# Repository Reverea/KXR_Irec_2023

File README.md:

# KXR_Irec_2023
Knights Experimental Rocketry payloads resources for IREC 2023

## Structure
The payloads system of the UCF KXR 2023 IREC Hybrid Rocket will only be used for experiments, video recording/transmission, and data recording/transmission. All recovery hardware will be commercial. 

The payloads system consists of three main PCBs, each with a specialized purpose to allow for modularity. The PCBs will communicate over a CAN bus. The three PCBs are as follows:
1. Power Board: Regulate 4s Lipo to 12v, measure current and voltage and different points, control and distribute power to different systems. 
2. Main Avionics Board: Gather sensor data, record sensor data, manage data between different boards.
3. Nosecone Board: Receive GPS data, transmit/receive telemetry, control power to video RF amp. 

This repository contains the Nosecone and Power PCBs as those were the two that I designed.

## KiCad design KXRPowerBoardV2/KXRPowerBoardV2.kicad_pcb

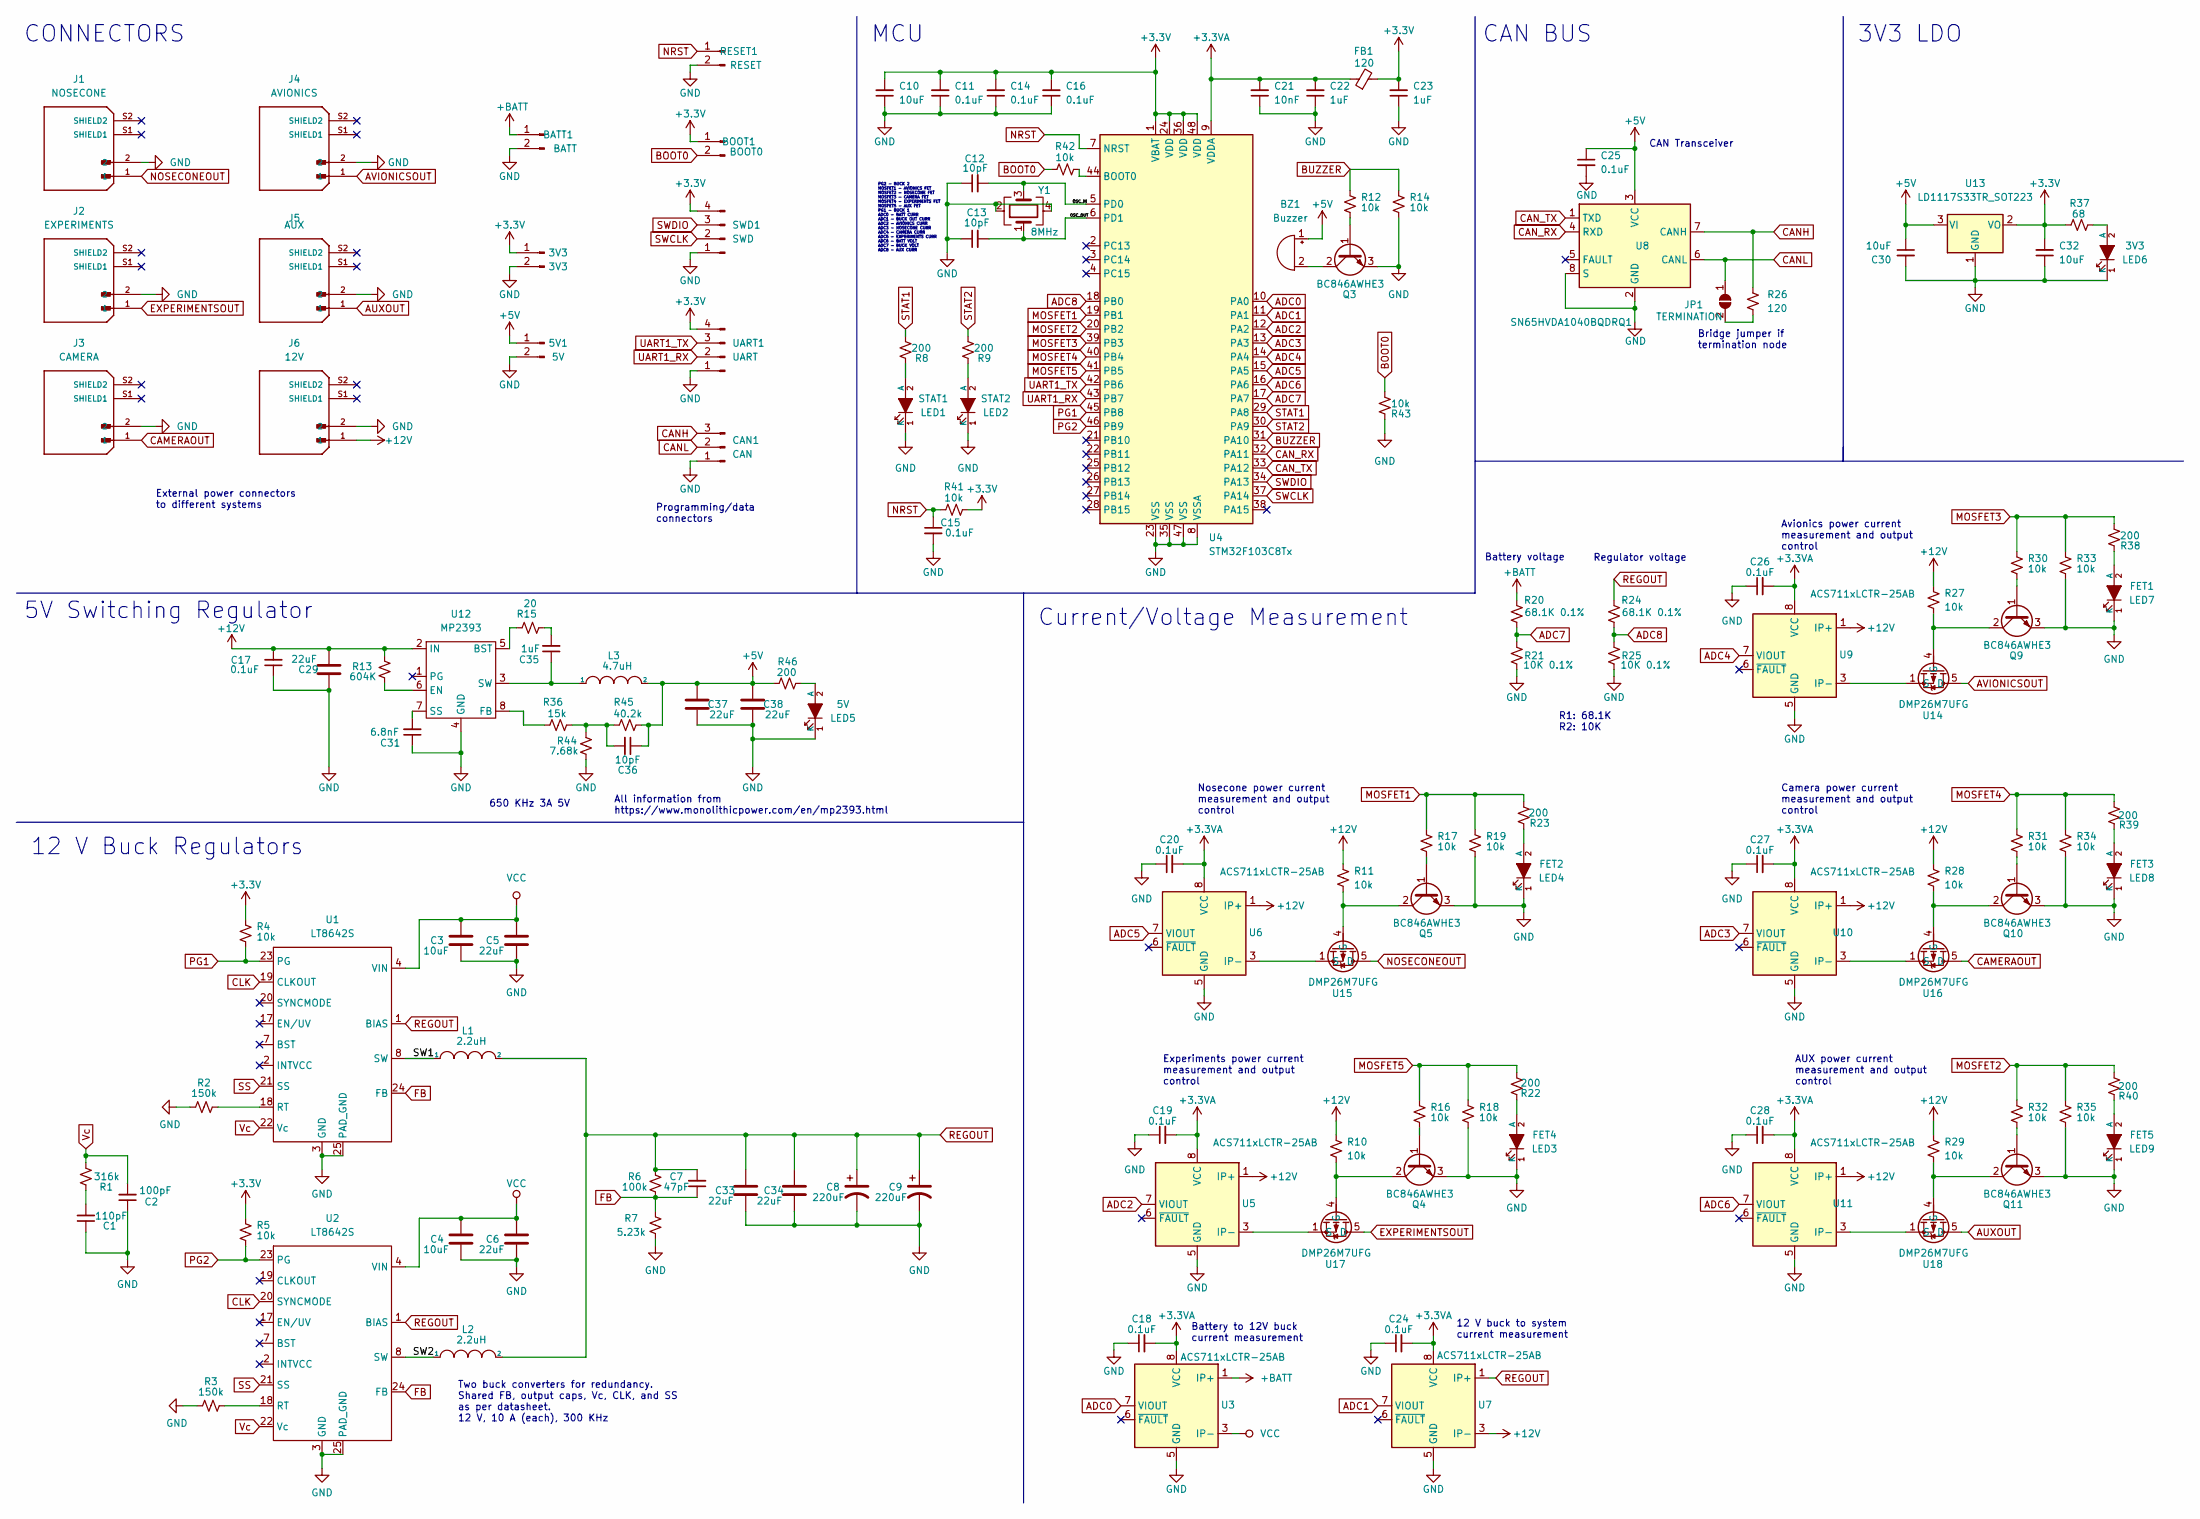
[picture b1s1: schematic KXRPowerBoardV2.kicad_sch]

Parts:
3V3: 3V3; PinHeader_1x02_P2.54mm_Vertical
5V1: 5V; PinHeader_1x02_P2.54mm_Vertical
BATT1: BATT; Molex_KK-396_A-41791-0002_1x02_P3.96mm_Vertical
BOOT1: BOOT0; PinHeader_1x02_P2.54mm_Vertical
BZ1: Buzzer; MagneticBuzzer_PUI_AT-0927-TT-6-R
C1: 110pF; C_0402_1005Metric
C2: 100pF; C_0402_1005Metric
C3, C4, C30, C32: 10uF; C_1206_3216Metric
C5, C6, C29, C33, C34, C37, C38: 22uF; C_1210_3225Metric
C7: 47pF; C_0402_1005Metric
C8, C9: 220uF; CP_Radial_D8.0mm_P3.50mm
C10: 10uF; C_0805_2012Metric
C11, C14, C15, C16, C17, C18, C19, C20, C24, C25, C26, C27, C28: 0.1uF; C_0402_1005Metric
C12, C13, C36: 10pF; C_0402_1005Metric
C21: 10nF; C_0402_1005Metric
C22, C23, C35: 1uF; C_0402_1005Metric
C31: 6.8nF; C_0402_1005Metric
CAN1: CAN; Molex_PicoBlade_53048-0310_1x03_P1.25mm_Horizontal
FB1: 120; L_0603_1608Metric
J1: NOSECONE; MOLEX_436500203; PARTREV F3
J2: EXPERIMENTS; MOLEX_436500203; PARTREV F3
J3: CAMERA; MOLEX_436500203; PARTREV F3
J4: AVIONICS; MOLEX_436500203; PARTREV F3
J5: AUX; MOLEX_436500203; PARTREV F3
J6: 12V; MOLEX_436500203; PARTREV F3
JP1: TERMINATION; SolderJumper-2_P1.3mm_Open_RoundedPad1.0x1.5mm
L1, L2: 2.2uH; XAL7070-222MEC
L3: 4.7uH; MGAH06034R7M
LED1: STAT1; LED_0603_1608Metric
LED2: STAT2; LED_0603_1608Metric
LED3: FET4; LED_0603_1608Metric
LED4: FET2; LED_0603_1608Metric
LED5: 5V; LED_0603_1608Metric
LED6: 3V3; LED_0603_1608Metric
LED7: FET1; LED_0603_1608Metric
LED8: FET3; LED_0603_1608Metric
LED9: FET5; LED_0603_1608Metric
Q3, Q4, Q5, Q9, Q10, Q11: BC846AWHE3; SOT-323_SC-70
R1: 316k; R_0402_1005Metric
R2, R3: 150k; R_0402_1005Metric
R4, R5, R10, R11, R12, R14, R16, R17, R18, R19, R27, R28, R29, R30, R31, R32, R33, R34, R35, R41, R42, R43: 10k; R_0402_1005Metric
R6: 100k; R_0402_1005Metric
R7: 5.23k; R_0402_1005Metric
R8, R9, R22, R23, R38, R39, R40, R46: 200; R_0402_1005Metric
R13: 604K; R_0402_1005Metric
R15: 20; R_0402_1005Metric
R20, R24: 68.1K 0.1%; R_0402_1005Metric
R21, R25: 10K 0.1%; R_0402_1005Metric
R26: 120; R_0402_1005Metric
R36: 15k; R_0402_1005Metric
R37: 68; R_0402_1005Metric
R44: 7.68k; R_0402_1005Metric
R45: 40.2k; R_0402_1005Metric
RESET1: RESET; PinHeader_1x02_P2.54mm_Vertical
SWD1: SWD; PinHeader_1x04_P2.54mm_Vertical
U1, U2: LT8642S; LT8642SIVPBF
U3, U5, U6, U7, U9, U10, U11: ACS711xLCTR-25AB; SOIC-8_3.9x4.9mm_P1.27mm
U4: STM32F103C8Tx; LQFP-48_7x7mm_P0.5mm
U8: SN65HVDA1040BQDRQ1; SOIC-8_3.9x4.9mm_P1.27mm
U12: MP2393; SOTFL50P160X60-8N
U13: LD1117S33TR_SOT223; SOT-223-3_TabPin2
U14, U15, U16, U17, U18: DMP26M7UFG; Diodes_PowerDI3333-8
UART1: UART; PinHeader_1x04_P2.54mm_Vertical
Y1: 8MHz; Crystal_SMD_3225-4Pin_3.2x2.5mm

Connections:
Vc: C2.2, R1.1, U1.22 (Vc), U2.22 (Vc)
+3.3VA: C18.2, C19.2, C20.2, C21.2, C22.2, C24.2, C26.2, C27.2, C28.2, FB1.1, U3.8 (VCC), U4.9 (VDDA), U5.8 (VCC), U6.8 (VCC), U7.8 (VCC), U9.8 (VCC), U10.8 (VCC), U11.8 (VCC)
+5V: 5V1.1, BZ1.1 (-), C25.1, C30.1, C36.1, C37.1, C38.1, L3.2, R45.2, R46.1, U8.3 (VCC), U13.3 (VI)
+BATT: BATT1.1, R20.1, U3.1 (IP+), U3.2 (IP+)
/OSC_IN: C12.2, U4.5 (PD0), Y1.3
/OSC_OUT: C13.2, U4.6 (PD1), Y1.1
/SW1: L1.1, U1.8 (SW), U1.9 (SW), U1.10 (SW), U1.11 (SW), U1.12 (SW)
/SW2: L2.1, U2.8 (SW), U2.9 (SW), U2.10 (SW), U2.11 (SW), U2.12 (SW)
ADC0: U3.7 (VIOUT), U4.10 (PA0)
ADC1: U4.11 (PA1), U7.7 (VIOUT)
ADC2: U4.12 (PA2), U5.7 (VIOUT)
ADC3: U4.13 (PA3), U10.7 (VIOUT)
ADC4: U4.14 (PA4), U9.7 (VIOUT)
ADC5: U4.15 (PA5), U6.7 (VIOUT)
ADC6: U4.16 (PA6), U11.7 (VIOUT)
ADC7: R20.2, R21.1, U4.17 (PA7)
ADC8: R24.2, R25.1, U4.18 (PB0)
AUXOUT: J5.1, U18.5 (D)
AVIONICSOUT: J4.1, U14.5 (D)
BOOT0: BOOT1.2, R42.2, R43.1
BUZZER: R12.1, R14.1, U4.31 (PA10)
CAMERAOUT: J3.1, U16.5 (D)
CANH: CAN1.3, R26.1, U8.7 (CANH)
CANL: CAN1.2, JP1.1 (A), U8.6 (CANL)
CAN_RX: U4.32 (PA11), U8.4 (RXD)
CAN_TX: U4.33 (PA12), U8.1 (TXD)
CLK: U1.19 (CLKOUT), U2.20 (SYNCMODE)
EXPERIMENTSOUT: J2.1, U17.5 (D)
FB: C7.1, R6.2, R7.1, U1.24 (FB), U2.24 (FB)
GND: 3V3.2, 5V1.2, BATT1.2, C1.1, C2.1, C3.2, C4.2, C5.2, C6.2, C8.2, C9.2, C10.1, C11.1, C12.1, C13.1, C14.1, C15.2, C16.1, C17.1, C18.1, C19.1, C20.1, C21.1, C22.1, C23.1, C24.1, C25.2, C26.1, C27.1, C28.1, C29.1, C30.2, C31.1, C32.1, C33.2, C34.2, C37.2, C38.2, CAN1.1, J1.2, J2.2, J3.2, J4.2, J5.2, J6.2, LED1.1 (K), LED2.1 (K), LED3.1 (K), LED4.1 (K), LED5.1 (K), LED6.1 (K), LED7.1 (K), LED8.1 (K), LED9.1 (K), Q3.3 (E), Q4.3 (E), Q5.3 (E), Q9.3 (E), Q10.3 (E), Q11.3 (E), R2.2, R3.2, R7.2, R14.2, R18.2, R19.2, R21.2, R25.2, R33.2, R34.2, R35.2, R43.2, R44.1, RESET1.2, SWD1.1, U1.3 (GND), U1.16 (GND), U1.25 (PAD_GND), U1.26 (PAD_GND), U1.27 (PAD_GND), U1.28 (PAD_GND), U2.3 (GND), U2.16 (GND), U2.25 (PAD_GND), U2.26 (PAD_GND), U2.27 (PAD_GND), U2.28 (PAD_GND), U3.5 (GND), U4.8 (VSSA), U4.23 (VSS), U4.35 (VSS), U4.47 (VSS), U5.5 (GND), U6.5 (GND), U7.5 (GND), U8.2 (GND), U8.8 (S), U9.5 (GND), U10.5 (GND), U11.5 (GND), U12.4 (GND), U13.1 (GND), UART1.1, Y1.2, Y1.4; also elsewhere on the board
MOSFET1: R17.1, R19.1, R23.1, U4.19 (PB1)
MOSFET2: R32.1, R35.1, R40.1, U4.20 (PB2)
MOSFET3: R30.1, R33.1, R38.1, U4.39 (PB3)
MOSFET4: R31.1, R34.1, R39.1, U4.40 (PB4)
MOSFET5: R16.1, R18.1, R22.1, U4.41 (PB5)
NOSECONEOUT: J1.1, U15.5 (D)
NRST: C15.1, R41.2, RESET1.1, U4.7 (NRST)
unnamed: BZ1.2 (+), Q3.2 (C)
unnamed: C1.2, R1.2
unnamed: C31.2, U12.7 (SS)
unnamed: C35.1, L3.1, U12.3 (SW)
unnamed: C35.2, R15.2
unnamed: C36.2, R36.2, R44.2, R45.1
unnamed: JP1.2 (B), R26.2
unnamed: LED1.2 (A), R8.2
unnamed: LED2.2 (A), R9.2
unnamed: LED3.2 (A), R22.2
unnamed: LED4.2 (A), R23.2
unnamed: LED5.2 (A), R46.2
unnamed: LED6.2 (A), R37.2
unnamed: LED7.2 (A), R38.2
unnamed: LED8.2 (A), R39.2
unnamed: LED9.2 (A), R40.2
unnamed: Q3.1 (B), R12.2
unnamed: Q4.1 (B), R16.2
unnamed: Q4.2 (C), R10.2, U17.4 (G)
unnamed: Q5.1 (B), R17.2
unnamed: Q5.2 (C), R11.2, U15.4 (G)
unnamed: Q9.1 (B), R30.2
unnamed: Q9.2 (C), R27.2, U14.4 (G)
unnamed: Q10.1 (B), R31.2
unnamed: Q10.2 (C), R28.2, U16.4 (G)
unnamed: Q11.1 (B), R32.2
unnamed: Q11.2 (C), R29.2, U18.4 (G)
unnamed: R2.1, U1.18 (RT)
unnamed: R3.1, U2.18 (RT)
unnamed: R13.1, U12.6 (EN)
unnamed: R15.1, U12.5 (BST)
unnamed: R36.1, U12.8 (FB)
unnamed: R42.1, U4.44 (BOOT0)
unnamed: U10.3 (IP-), U10.4 (IP-), U16.1 (S), U16.2 (S), U16.3 (S)
unnamed: U11.3 (IP-), U11.4 (IP-), U18.1 (S), U18.2 (S), U18.3 (S)
unnamed: U9.3 (IP-), U9.4 (IP-), U14.1 (S), U14.2 (S), U14.3 (S)
unnamed: U6.3 (IP-), U6.4 (IP-), U15.1 (S), U15.2 (S), U15.3 (S)
unnamed: U5.3 (IP-), U5.4 (IP-), U17.1 (S), U17.2 (S), U17.3 (S)
PG1: R4.2, U1.23 (PG), U4.45 (PB8)
PG2: R5.2, U2.23 (PG), U4.46 (PB9)
REGOUT: C7.2, C8.1, C9.1, C33.1, C34.1, L1.2, L2.2, R6.1, R24.1, U1.1 (BIAS), U2.1 (BIAS), U7.1 (IP+), U7.2 (IP+)
SS: U1.21 (SS), U2.21 (SS)
STAT1: R8.1, U4.29 (PA8)
STAT2: R9.1, U4.30 (PA9)
SWCLK: SWD1.2, U4.37 (PA14)
SWDIO: SWD1.3, U4.34 (PA13)
UART1_RX: U4.43 (PB7), UART1.2
UART1_TX: U4.42 (PB6), UART1.3
VCC: C3.1, C4.1, C5.1, C6.1, U1.4 (VIN), U1.5 (VIN), U1.6 (VIN), U1.13 (VIN), U1.14 (VIN), U1.15 (VIN), U2.4 (VIN), U2.5 (VIN), U2.6 (VIN), U2.13 (VIN), U2.14 (VIN), U2.15 (VIN), U3.3 (IP-), U3.4 (IP-)

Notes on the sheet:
PG2 - BUCK 2 MOSFET1 - AVIONICS FET MOSFET2 - NOSECONE FET MOSFET3 - CAMERA FET MOSFET4 - EXPERIMENTS FET MOSFET5 - AUX FET PG1 - BUCK 1 ADC0 - BATT CURR ADC1 - BUCK OUT CURR ADC2 - AVIONICS CURR ADC3 - NOSECONE CURR ADC4 - CAMERA CURR ADC5 - EXPERIMENTS CURR ADC6 - BATT VOLT ADC7 - BUCK VOLT ADC8 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
R1: 68.1K R2: 10K
Camera power current measurement and output control
CAN BUS
Experiments power current measurement and output control
12 V buck to system current measurement
Current/Voltage Measurement
Regulator voltage
Nosecone power current measurement and output control
AUX power current measurement and output control
Two buck converters for redundancy. Shared FB, output caps, Vc, CLK, and SS as per datasheet. 12 V, 10 A (each), 300 KHz
12 V Buck Regulators
Avionics power current measurement and output control
Battery voltage
All information from https://www.monolithicpower.com/en/mp2393.html
CAN Transceiver
3V3 LDO
5V Switching Regulator
Programming/data connectors
CONNECTORS
Bridge jumper if termination node
MCU
650 KHz 3A 5V
External power connectors to different systems
Battery to 12V buck current measurement

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
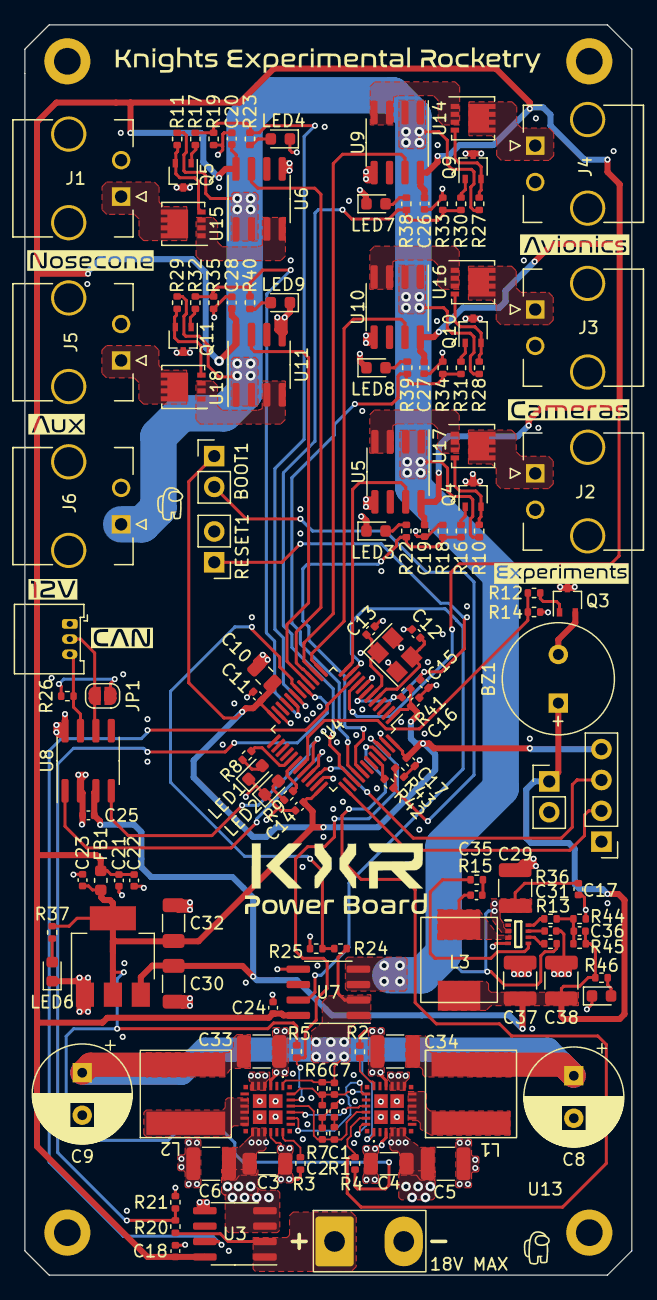
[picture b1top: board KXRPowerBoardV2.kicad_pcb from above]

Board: 4 copper layers, 50.0 x 103.0 mm, 137 parts (0 on the bottom side), 86 nets.

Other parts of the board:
C17#2: 0.1uF; C_0402_1005Metric

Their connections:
GND: C17#2.1; also elsewhere on the board

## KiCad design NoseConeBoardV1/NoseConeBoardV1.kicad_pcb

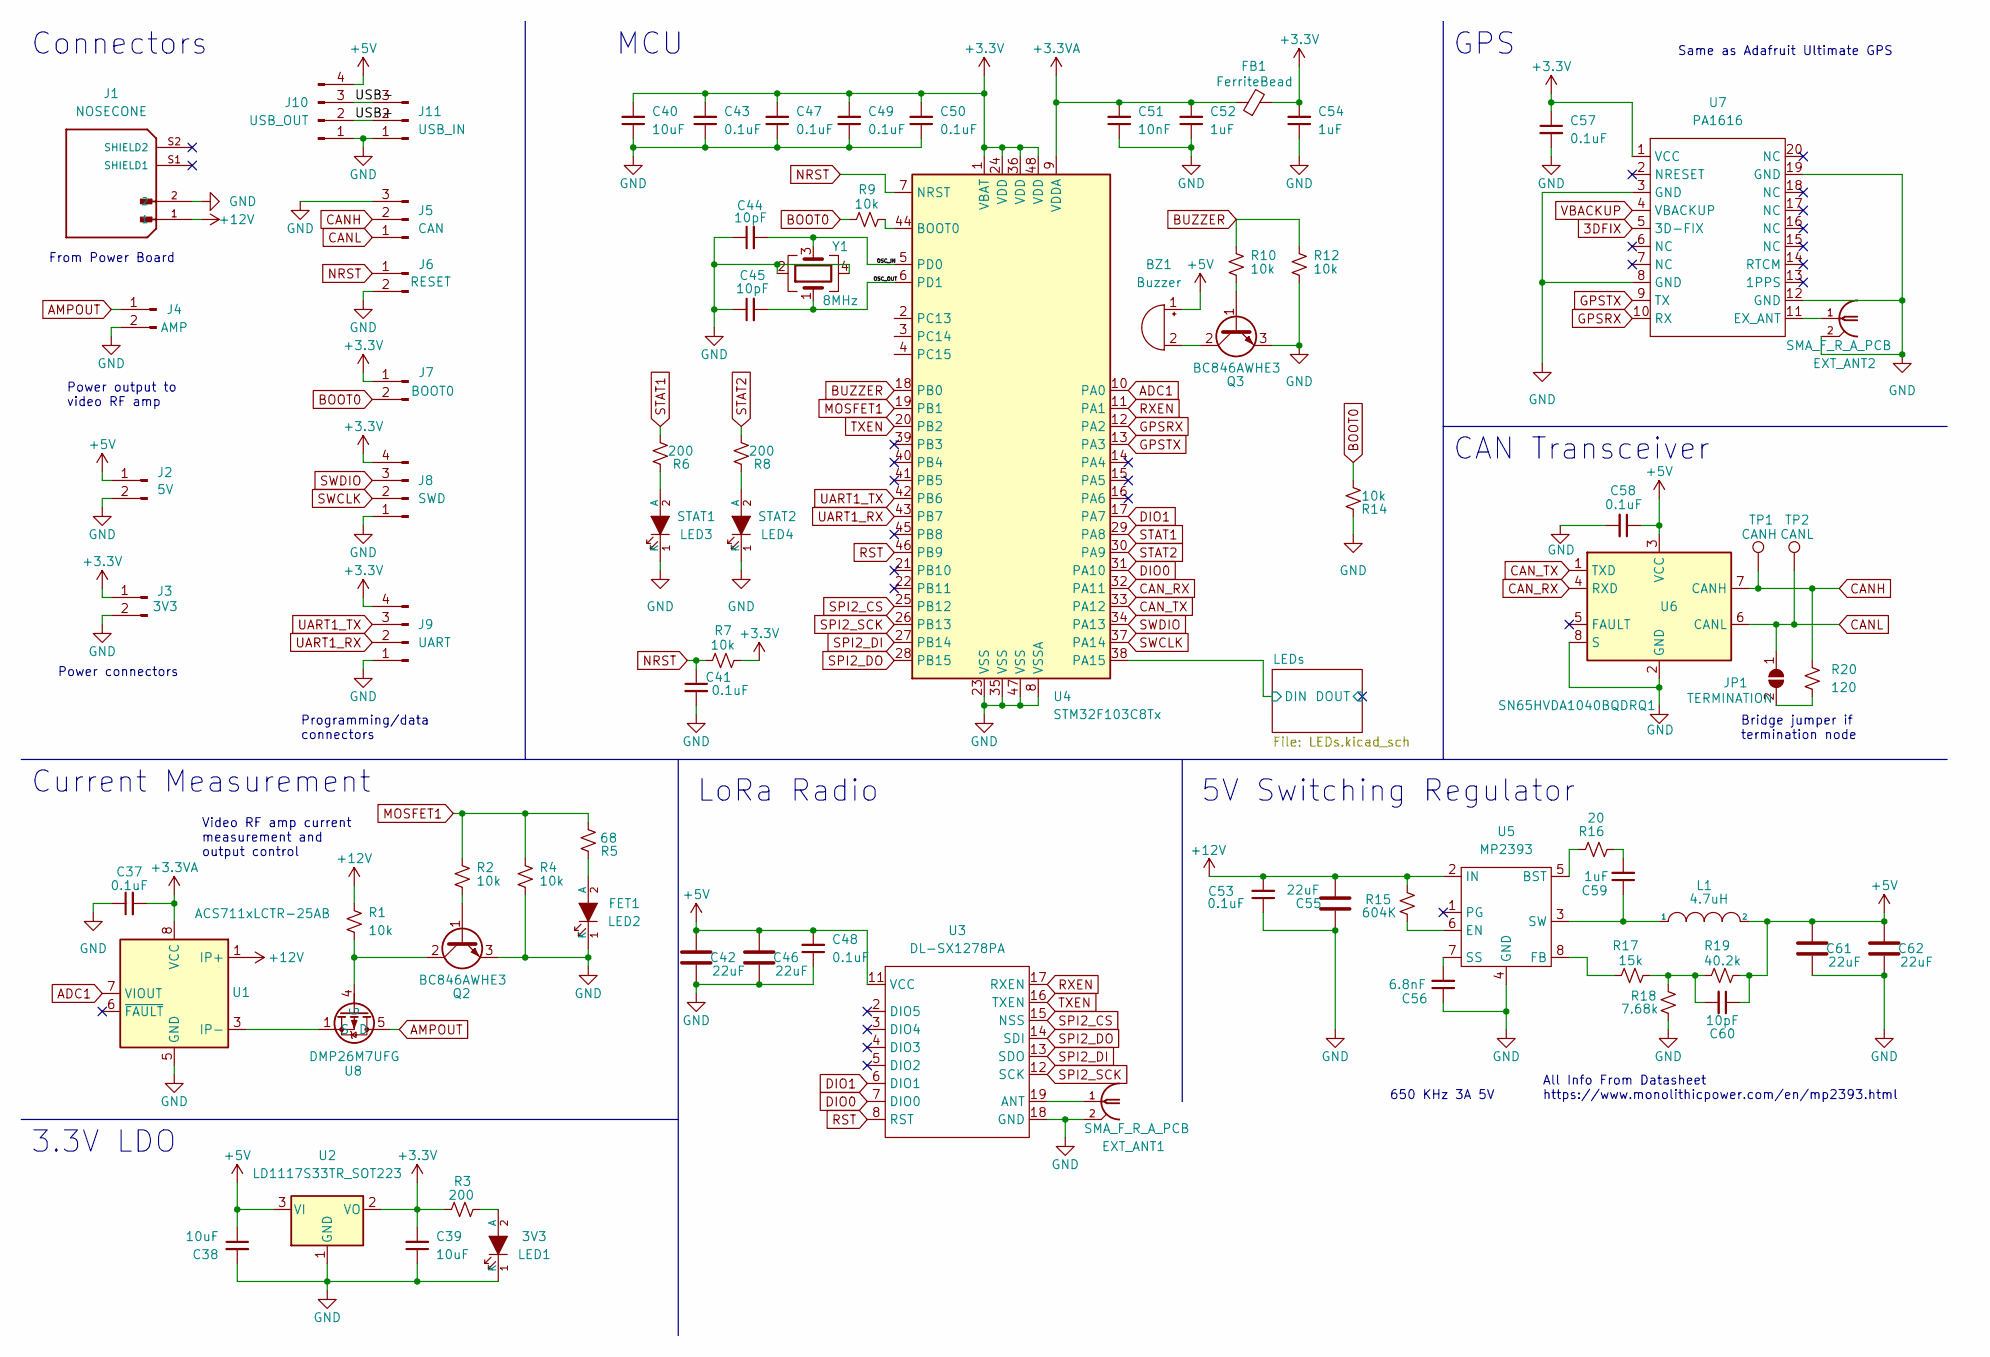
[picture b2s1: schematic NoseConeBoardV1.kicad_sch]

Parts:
BZ1: Buzzer; MagneticBuzzer_PUI_AT-0927-TT-6-R
C37, C41, C43, C47, C48, C49, C50, C53, C57, C58: 0.1uF; C_0402_1005Metric
C38, C39, C40: 10uF; C_1206_3216Metric
C42, C46, C55, C61, C62: 22uF; C_1210_3225Metric
C44, C45, C60: 10pF; C_0402_1005Metric
C51: 10nF; C_0402_1005Metric
C52, C54, C59: 1uF; C_0402_1005Metric
C56: 6.8nF; C_0402_1005Metric
EXT_ANT1, EXT_ANT2: SMA_F_R_A_PCB; SMA_Amphenol_901-144_Vertical
FB1: FerriteBead; L_0603_1608Metric
J1: NOSECONE; MOLEX_436500203; PARTREV F3
J2: 5V; PinSocket_1x02_P2.54mm_Vertical
J3: 3V3; PinSocket_1x02_P2.54mm_Vertical
J4: AMP; PinSocket_1x02_P2.54mm_Vertical
J5: CAN; Molex_PicoBlade_53048-0310_1x03_P1.25mm_Horizontal
J6: RESET; PinSocket_1x02_P2.54mm_Vertical
J7: BOOT0; PinSocket_1x02_P2.54mm_Vertical
J8: SWD; PinSocket_1x04_P2.54mm_Vertical
J9: UART; PinSocket_1x04_P2.54mm_Vertical
J10: USB_OUT; PinSocket_1x04_P2.54mm_Vertical
J11: USB_IN; Molex_PicoBlade_53048-0310_1x03_P1.25mm_Horizontal
JP1: TERMINATION; SolderJumper-2_P1.3mm_Open_RoundedPad1.0x1.5mm
L1: 4.7uH; MGAH06034R7M
LED1: 3V3; LED_0603_1608Metric
LED2: FET1; LED_0603_1608Metric
LED3: STAT1; LED_0603_1608Metric
LED4: STAT2; LED_0603_1608Metric
Q2, Q3: BC846AWHE3; SOT-323_SC-70
R1, R2, R4, R7, R9, R10, R12, R14: 10k; R_0402_1005Metric
R3, R6, R8: 200; R_0402_1005Metric
R5: 68; R_0402_1005Metric
R15: 604K; R_0402_1005Metric
R16: 20; R_0402_1005Metric
R17: 15k; R_0402_1005Metric
R18: 7.68k; R_0402_1005Metric
R19: 40.2k; R_0402_1005Metric
R20: 120; R_0402_1005Metric
TP1: CANH; TestPoint_Pad_D1.0mm
TP2: CANL; TestPoint_Pad_D1.0mm
U1: ACS711xLCTR-25AB; SOIC-8_3.9x4.9mm_P1.27mm
U2: LD1117S33TR_SOT223; SOT-223-3_TabPin2
U3: DL-SX1278PA
U4: STM32F103C8Tx; LQFP-48_7x7mm_P0.5mm
U5: MP2393; SOTFL50P160X60-8N
U6: SN65HVDA1040BQDRQ1; SOIC-8_3.9x4.9mm_P1.27mm
U7: PA1616
U8: DMP26M7UFG; Diodes_PowerDI3333-8
Y1: 8MHz; Crystal_SMD_3225-4Pin_3.2x2.5mm

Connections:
3DFIX: U7.5 (3D-FIX)
+3.3VA: C37.2, C51.2, C52.2, FB1.1, U1.8 (VCC), U4.9 (VDDA)
+3V3: C39.2, C40.2, C43.2, C47.2, C49.2, C50.2, C54.2, C57.1, FB1.2, J3.1, J7.1, J8.4, J9.4, R3.1, R7.1, U2.2 (VO), U4.1 (VBAT), U4.24 (VDD), U4.36 (VDD), U4.48 (VDD), U7.1 (VCC)
+5V: BZ1.1 (-), C38.1, C42.1, C46.1, C48.2, C58.1, C60.1, C61.1, C62.1, J2.1, J10.4, L1.2, R19.2, U2.3 (VI), U3.11 (VCC), U6.3 (VCC); also elsewhere on the board
+12V: C53.2, C55.2, J1.1, R1.1, R15.2, U1.1 (IP+), U1.2 (IP+), U5.2 (IN)
/LEDs/DIN: U4.38 (PA15); also elsewhere on the board
/OSC_IN: C44.2, U4.5 (PD0), Y1.3
/OSC_OUT: C45.2, U4.6 (PD1), Y1.1
/USB+: J10.2, J11.2
/USB-: J10.3, J11.3
ADC1: U1.7 (VIOUT), U4.10 (PA0)
AMPOUT: J4.1, U8.5 (D)
BOOT0: J7.2, R9.2, R14.1
BUZZER: R10.1, R12.1, U4.18 (PB0)
CANH: J5.2, R20.1, TP1.1, U6.7 (CANH)
CANL: J5.1, JP1.1 (A), TP2.1, U6.6 (CANL)
CAN_RX: U4.32 (PA11), U6.4 (RXD)
CAN_TX: U4.33 (PA12), U6.1 (TXD)
DIO0: U3.7 (DIO0), U4.31 (PA10)
DIO1: U3.6 (DIO1), U4.17 (PA7)
GND: C37.1, C38.2, C39.1, C40.1, C41.2, C42.2, C43.1, C44.1, C45.1, C46.2, C47.1, C48.1, C49.1, C50.1, C51.1, C52.1, C53.1, C54.1, C55.1, C56.1, C57.2, C58.2, C61.2, C62.2, EXT_ANT1.2, EXT_ANT1.3, EXT_ANT1.4, EXT_ANT1.5, EXT_ANT2.2, EXT_ANT2.3, EXT_ANT2.4, EXT_ANT2.5, J1.2, J2.2, J3.2, J4.2, J5.3, J6.2, J8.1, J9.1, J10.1, J11.1, LED1.1 (K), LED2.1 (K), LED3.1 (K), LED4.1 (K), Q2.3 (E), Q3.3 (E), R4.2, R12.2, R14.2, R18.1, U1.5 (GND), U2.1 (GND), U3.1 (GND), U3.9 (GND), U3.10 (GND), U3.18 (GND), U3.20 (GND), U3.21 (GND), U3.22 (GND), U4.8 (VSSA), U4.23 (VSS), U4.35 (VSS), U4.47 (VSS), U5.4 (GND), U6.2 (GND), U6.8 (S), U7.3 (GND), U7.8 (GND), U7.12 (GND), U7.19 (GND), Y1.2, Y1.4; also elsewhere on the board
GPSRX: U4.12 (PA2), U7.10 (RX)
GPSTX: U4.13 (PA3), U7.9 (TX)
MOSFET1: R2.1, R4.1, R5.1, U4.19 (PB1)
NRST: C41.1, J6.1, R7.2, U4.7 (NRST)
unnamed: BZ1.2 (+), Q3.2 (C)
unnamed: C56.2, U5.7 (SS)
unnamed: C59.1, L1.1, U5.3 (SW)
unnamed: C59.2, R16.2
unnamed: C60.2, R17.2, R18.2, R19.1
unnamed: EXT_ANT1.1, U3.19 (ANT)
unnamed: EXT_ANT2.1, U7.11 (EX_ANT)
unnamed: JP1.2 (B), R20.2
unnamed: LED1.2 (A), R3.2
unnamed: LED2.2 (A), R5.2
unnamed: LED3.2 (A), R6.2
unnamed: LED4.2 (A), R8.2
unnamed: Q2.1 (B), R2.2
unnamed: Q2.2 (C), R1.2, U8.4 (G)
unnamed: Q3.1 (B), R10.2
unnamed: R9.1, U4.44 (BOOT0)
unnamed: R15.1, U5.6 (EN)
unnamed: R16.1, U5.5 (BST)
unnamed: R17.1, U5.8 (FB)
unnamed: U1.3 (IP-), U1.4 (IP-), U8.1 (S), U8.2 (S), U8.3 (S)
RST: U3.8 (RST), U4.46 (PB9)
RXEN: U3.17 (RXEN), U4.11 (PA1)
SPI2_CS: U3.15 (NSS), U4.25 (PB12)
SPI2_DI: U3.13 (SDO), U4.27 (PB14)
SPI2_DO: U3.14 (SDI), U4.28 (PB15)
SPI2_SCK: U3.12 (SCK), U4.26 (PB13)
STAT1: R6.1, U4.29 (PA8)
STAT2: R8.1, U4.30 (PA9)
SWCLK: J8.2, U4.37 (PA14)
SWDIO: J8.3, U4.34 (PA13)
TXEN: U3.16 (TXEN), U4.20 (PB2)
UART1_RX: J9.2, U4.43 (PB7)
UART1_TX: J9.3, U4.42 (PB6)
VBACKUP: U7.4 (VBACKUP)

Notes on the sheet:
CAN Transceiver
Video RF amp current measurement and output control
5V Switching Regulator
Power connectors
LoRa Radio
MCU
3.3V LDO
Connectors
All Info From Datasheet https://www.monolithicpower.com/en/mp2393.html
Programming/data connectors
Current Measurement
Power output to video RF amp
Same as Adafruit Ultimate GPS
Bridge jumper if termination node
GPS
650 KHz 3A 5V
From Power Board

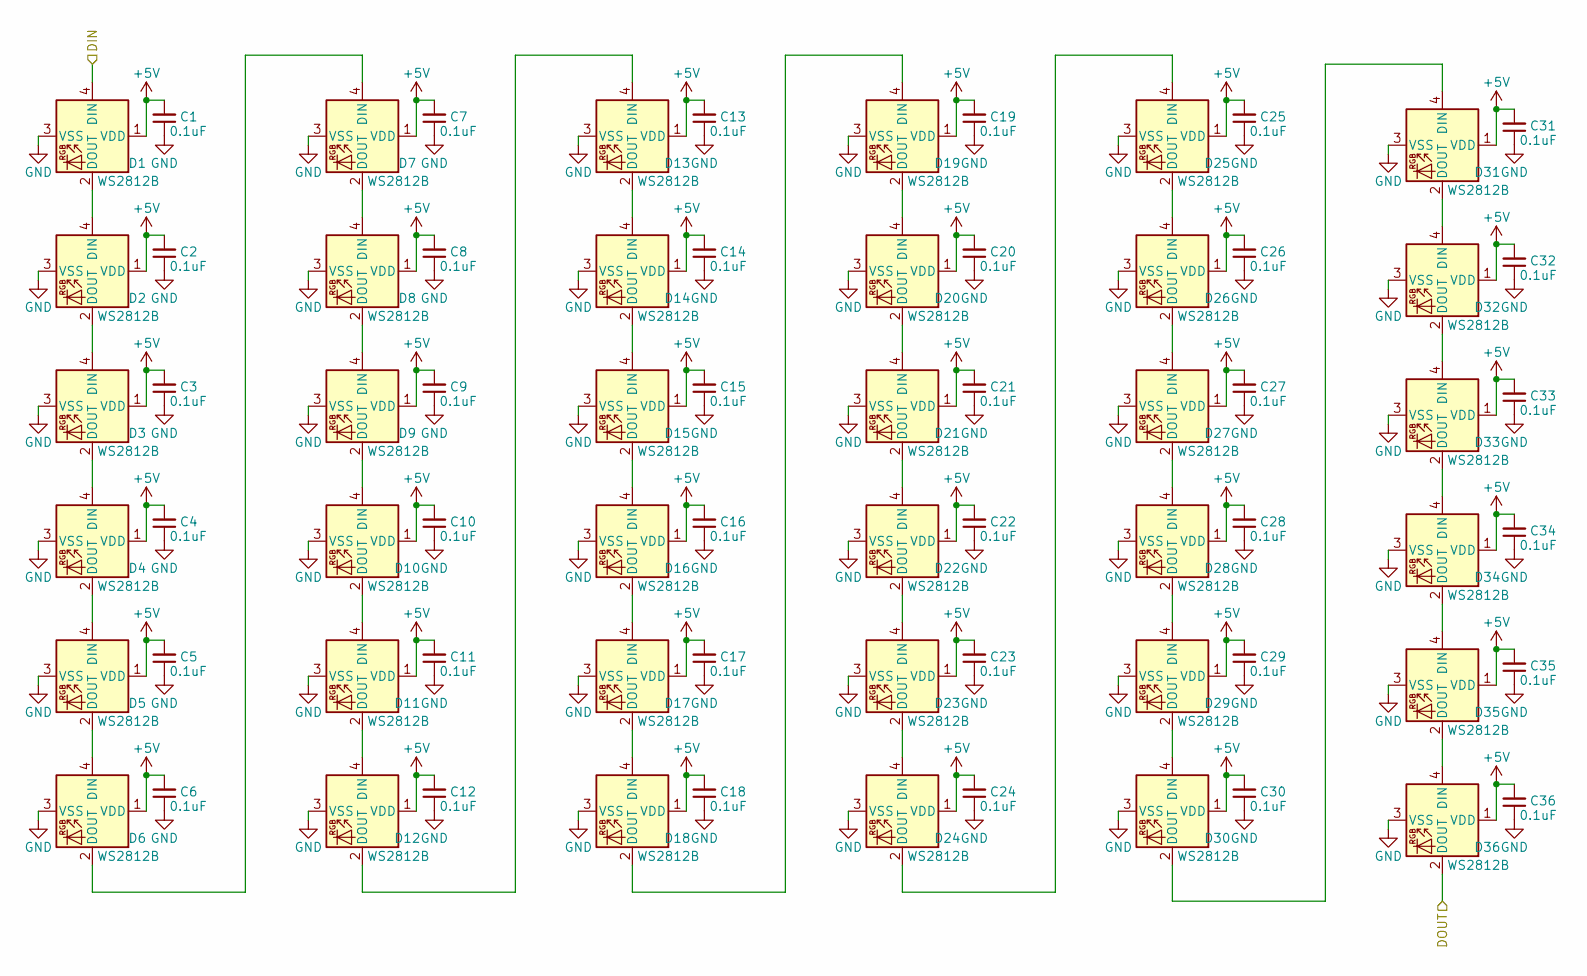
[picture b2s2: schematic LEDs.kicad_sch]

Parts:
C1, C2, C3, C4, C5, C6, C7, C8, C9, C10, C11, C12, C13, C14, C15, C16, C17, C18, C19, C20, C21, C22, C23, C24, C25, C26, C27, C28, C29, C30, C31, C32, C33, C34, C35, C36: 0.1uF; C_0402_1005Metric
D1, D2, D3, D4, D5, D6, D7, D8, D9, D10, D11, D12, D13, D14, D15, D16, D17, D18, D19, D20, D21, D22, D23, D24, D25, D26, D27, D28, D29, D30, D31, D32, D33, D34, D35, D36: WS2812B; LED_WS2812B_PLCC4_5.0x5.0mm_P3.2mm

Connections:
+5V: C1.2, C2.2, C3.2, C4.2, C5.2, C6.2, C7.2, C8.2, C9.2, C10.2, C11.2, C12.2, C13.2, C14.2, C15.2, C16.2, C17.2, C18.2, C19.2, C20.2, C21.2, C22.2, C23.2, C24.2, C25.2, C26.2, C27.2, C28.2, C29.2, C30.2, C31.2, C32.2, C33.2, C34.2, C35.2, C36.2, D1.1 (VDD), D2.1 (VDD), D3.1 (VDD), D4.1 (VDD), D5.1 (VDD), D6.1 (VDD), D7.1 (VDD), D8.1 (VDD), D9.1 (VDD), D10.1 (VDD), D11.1 (VDD), D12.1 (VDD), D13.1 (VDD), D14.1 (VDD), D15.1 (VDD), D16.1 (VDD), D17.1 (VDD), D18.1 (VDD), D19.1 (VDD), D20.1 (VDD), D21.1 (VDD), D22.1 (VDD), D23.1 (VDD), D24.1 (VDD), D25.1 (VDD), D26.1 (VDD), D27.1 (VDD), D28.1 (VDD), D29.1 (VDD), D30.1 (VDD), D31.1 (VDD), D32.1 (VDD), D33.1 (VDD), D34.1 (VDD), D35.1 (VDD), D36.1 (VDD); also elsewhere on the board
/LEDs/DIN: D1.4 (DIN); also elsewhere on the board
/LEDs/DOUT: D36.2 (DOUT)
GND: C1.1, C2.1, C3.1, C4.1, C5.1, C6.1, C7.1, C8.1, C9.1, C10.1, C11.1, C12.1, C13.1, C14.1, C15.1, C16.1, C17.1, C18.1, C19.1, C20.1, C21.1, C22.1, C23.1, C24.1, C25.1, C26.1, C27.1, C28.1, C29.1, C30.1, C31.1, C32.1, C33.1, C34.1, C35.1, C36.1, D1.3 (VSS), D2.3 (VSS), D3.3 (VSS), D4.3 (VSS), D5.3 (VSS), D6.3 (VSS), D7.3 (VSS), D8.3 (VSS), D9.3 (VSS), D10.3 (VSS), D11.3 (VSS), D12.3 (VSS), D13.3 (VSS), D14.3 (VSS), D15.3 (VSS), D16.3 (VSS), D17.3 (VSS), D18.3 (VSS), D19.3 (VSS), D20.3 (VSS), D21.3 (VSS), D22.3 (VSS), D23.3 (VSS), D24.3 (VSS), D25.3 (VSS), D26.3 (VSS), D27.3 (VSS), D28.3 (VSS), D29.3 (VSS), D30.3 (VSS), D31.3 (VSS), D32.3 (VSS), D33.3 (VSS), D34.3 (VSS), D35.3 (VSS), D36.3 (VSS); also elsewhere on the board
unnamed: D1.2 (DOUT), D2.4 (DIN)
unnamed: D2.2 (DOUT), D3.4 (DIN)
unnamed: D3.2 (DOUT), D4.4 (DIN)
unnamed: D4.2 (DOUT), D5.4 (DIN)
unnamed: D5.2 (DOUT), D6.4 (DIN)
unnamed: D6.2 (DOUT), D7.4 (DIN)
unnamed: D7.2 (DOUT), D8.4 (DIN)
unnamed: D8.2 (DOUT), D9.4 (DIN)
unnamed: D10.2 (DOUT), D11.4 (DIN)
unnamed: D9.2 (DOUT), D10.4 (DIN)
unnamed: D11.2 (DOUT), D12.4 (DIN)
unnamed: D12.2 (DOUT), D13.4 (DIN)
unnamed: D13.2 (DOUT), D14.4 (DIN)
unnamed: D14.2 (DOUT), D15.4 (DIN)
unnamed: D15.2 (DOUT), D16.4 (DIN)
unnamed: D16.2 (DOUT), D17.4 (DIN)
unnamed: D17.2 (DOUT), D18.4 (DIN)
unnamed: D18.2 (DOUT), D19.4 (DIN)
unnamed: D19.2 (DOUT), D20.4 (DIN)
unnamed: D20.2 (DOUT), D21.4 (DIN)
unnamed: D21.2 (DOUT), D22.4 (DIN)
unnamed: D22.2 (DOUT), D23.4 (DIN)
unnamed: D23.2 (DOUT), D24.4 (DIN)
unnamed: D24.2 (DOUT), D25.4 (DIN)
unnamed: D25.2 (DOUT), D26.4 (DIN)
unnamed: D26.2 (DOUT), D27.4 (DIN)
unnamed: D27.2 (DOUT), D28.4 (DIN)
unnamed: D28.2 (DOUT), D29.4 (DIN)
unnamed: D29.2 (DOUT), D30.4 (DIN)
unnamed: D30.2 (DOUT), D31.4 (DIN)
unnamed: D31.2 (DOUT), D32.4 (DIN)
unnamed: D32.2 (DOUT), D33.4 (DIN)
unnamed: D33.2 (DOUT), D34.4 (DIN)
unnamed: D34.2 (DOUT), D35.4 (DIN)
unnamed: D35.2 (DOUT), D36.4 (DIN)

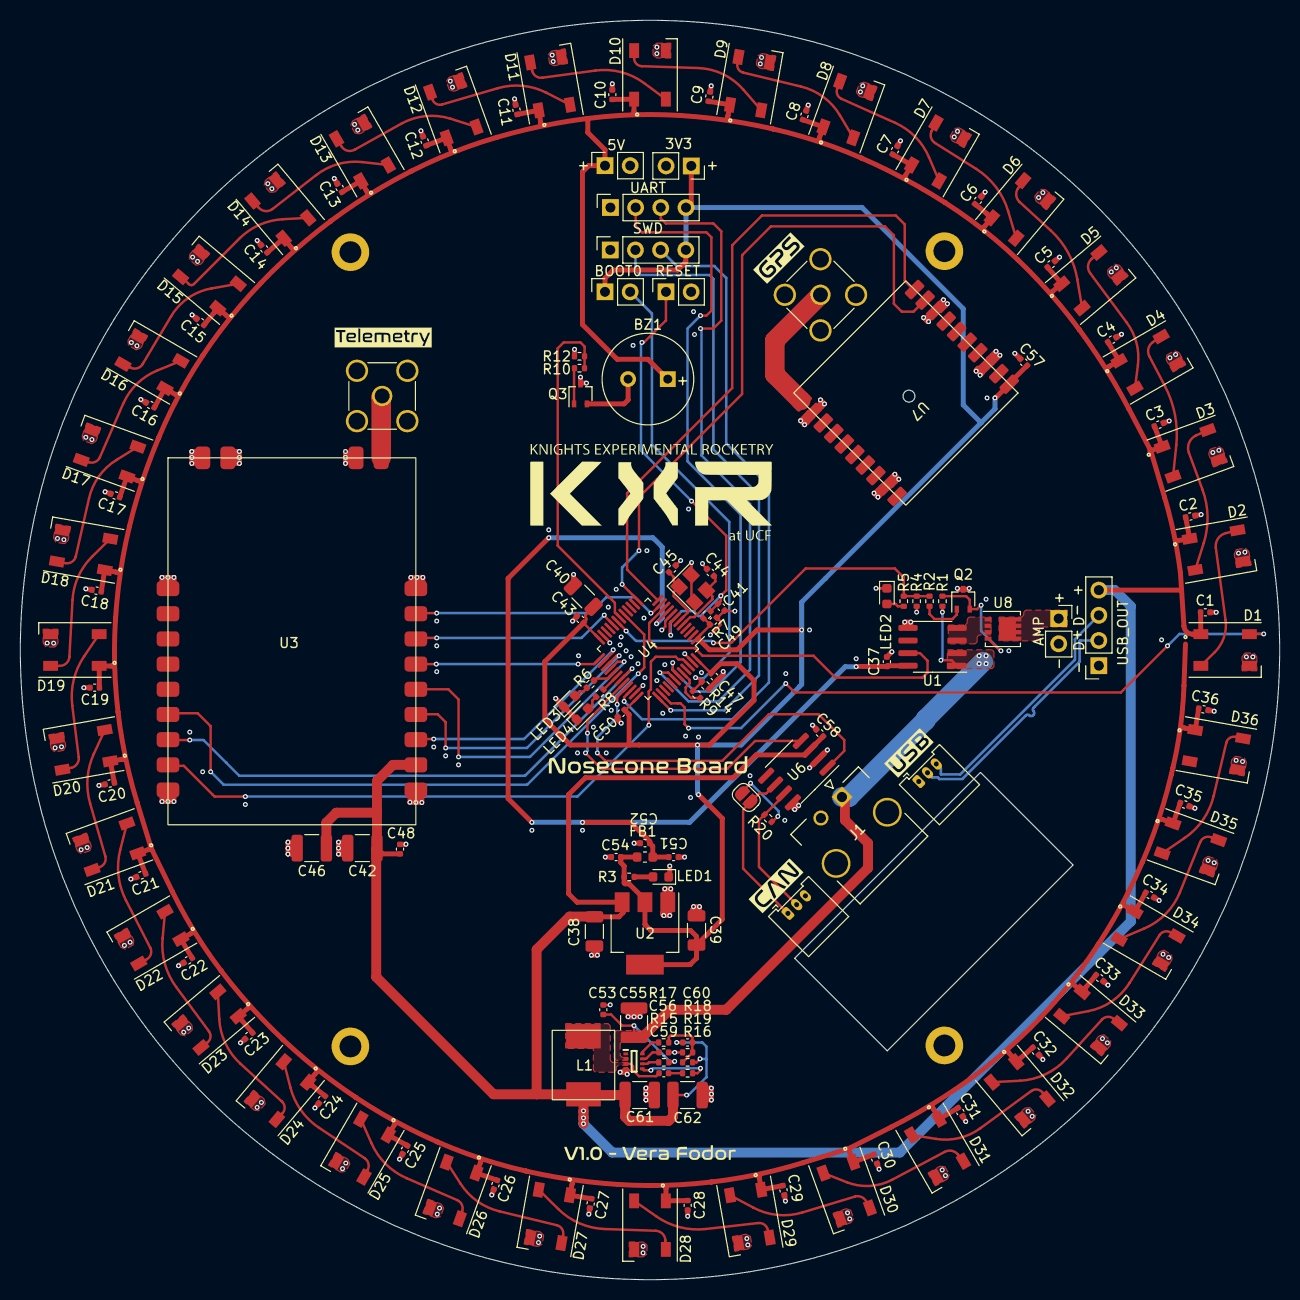
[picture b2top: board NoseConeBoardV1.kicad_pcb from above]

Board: 4 copper layers, 127.0 x 127.0 mm, 148 parts (0 on the bottom side), 92 nets.
